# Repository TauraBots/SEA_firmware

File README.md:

# SEA_firmware
Firmware utilizado no atuador de serra elástica

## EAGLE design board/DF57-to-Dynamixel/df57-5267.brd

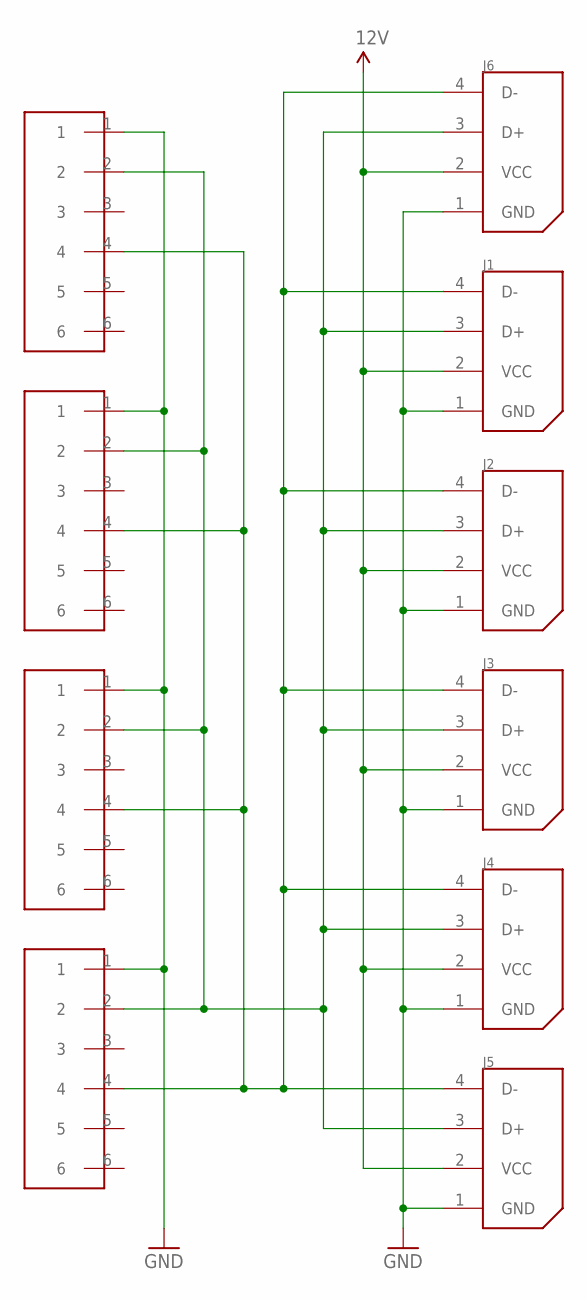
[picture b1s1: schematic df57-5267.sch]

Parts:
J1, J2, J3, J4, J5, J6: 22-03-5045; 5267-4
U$1, U$2, U$3, U$4: DF57-6P

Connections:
12V: J1.2 (VCC), J2.2 (VCC), J3.2 (VCC), J4.2 (VCC), J5.2 (VCC), J6.2 (VCC)
D+: J1.3 (D+), J2.3 (D+), J3.3 (D+), J4.3 (D+), J5.3 (D+), J6.3 (D+), U$1.2, U$2.2, U$3.2, U$4.2
D-: J1.4 (D-), J2.4 (D-), J3.4 (D-), J4.4 (D-), J5.4 (D-), J6.4 (D-), U$1.4, U$2.4, U$3.4, U$4.4
GND: J1.1 (GND), J2.1 (GND), J3.1 (GND), J4.1 (GND), J5.1 (GND), J6.1 (GND), U$1.1, U$2.1, U$3.1, U$4.1

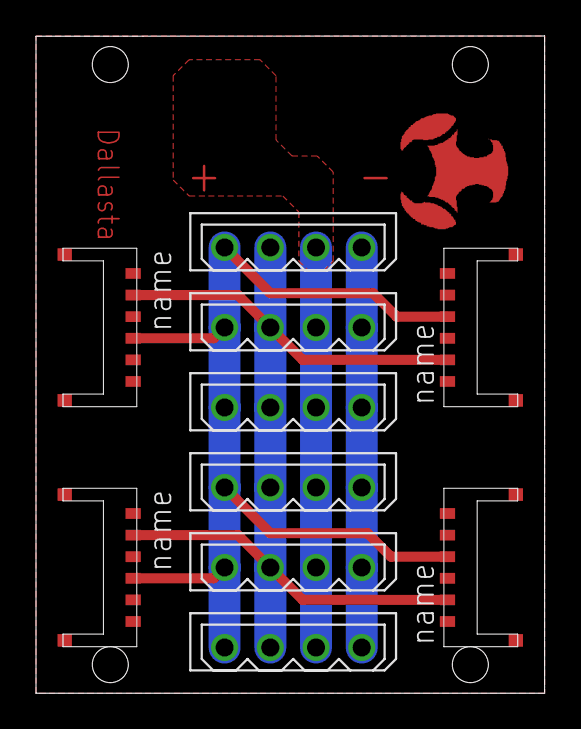
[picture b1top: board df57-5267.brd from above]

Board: 2 copper layers, 28.3 x 36.5 mm, 10 parts (0 on the bottom side), 4 nets.

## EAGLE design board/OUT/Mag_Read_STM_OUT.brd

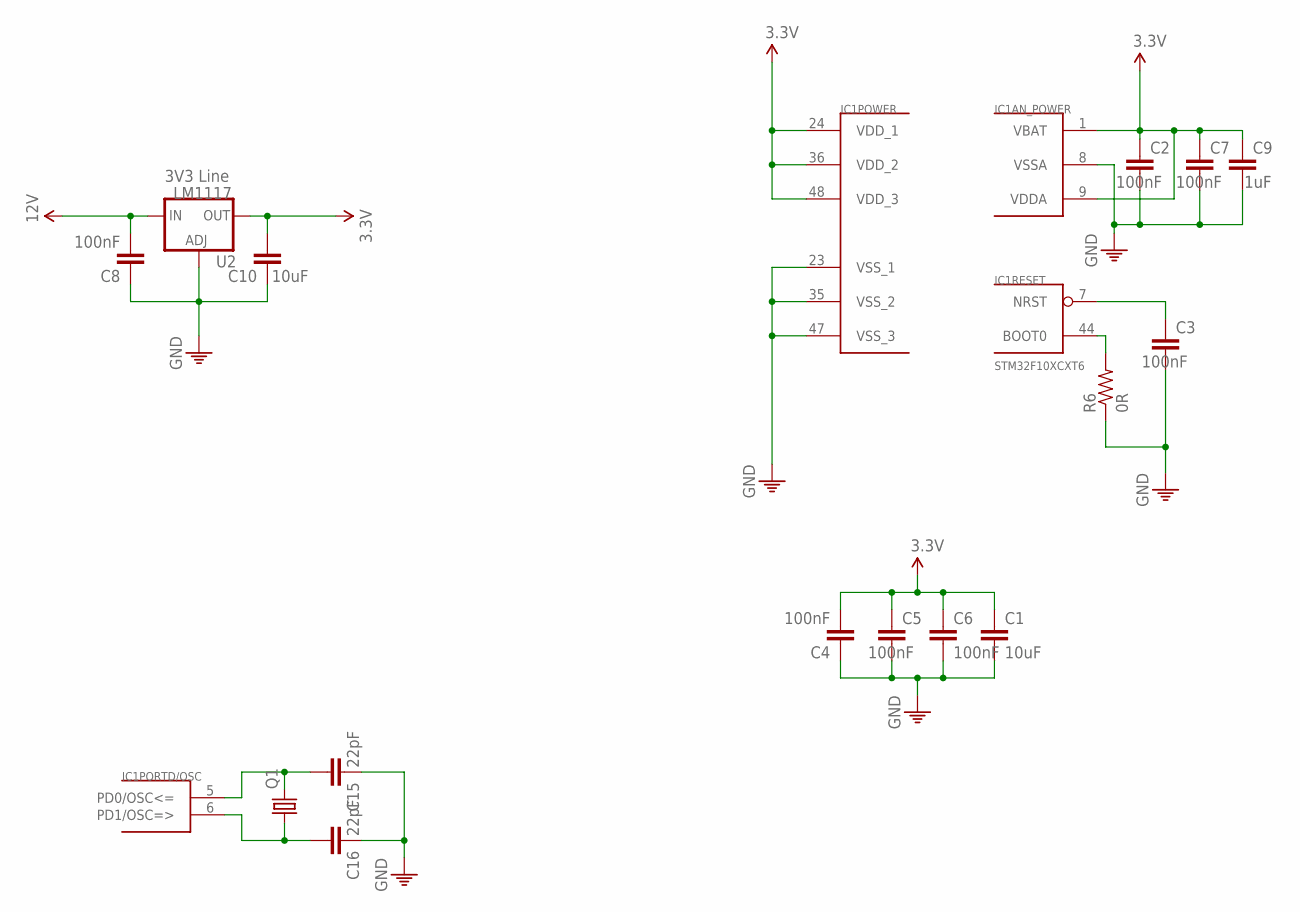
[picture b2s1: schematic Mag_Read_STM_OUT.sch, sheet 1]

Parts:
C1, C10: 10uF; C0603
C2, C3, C4, C5, C6, C7, C8: 100nF; C0603
C9: 1uF; C0603
C15, C16: 22pF; C0603
IC1: STM32F10XCXT6; TQFP48
Q1: CRYSTALCTS406; CTS406
R6: 0R; 0603-RES
U2: LM1117; SOT223

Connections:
3.3V: C1.1, C2.1, C4.2, C5.1, C6.1, C7.1, C9.1, C10.2, IC1.1 (VBAT), IC1.9 (VDDA), IC1.24 (VDD_1), IC1.36 (VDD_2), IC1.48 (VDD_3), U2.2 (OUT), U2.4 (OUT); also elsewhere on the board
12V: C8.2, U2.3 (IN); also elsewhere on the board
GND: C1.2, C2.2, C3.2, C4.1, C5.2, C6.2, C7.2, C8.1, C9.2, C10.1, C15.1, C16.1, IC1.8 (VSSA), IC1.23 (VSS_1), IC1.35 (VSS_2), IC1.47 (VSS_3), R6.1, U2.1 (ADJ); also elsewhere on the board
unnamed: C15.2, IC1.5 (PD0/OSC<=), Q1.3 (2)
unnamed: C16.2, IC1.6 (PD1/OSC=>), Q1.1
unnamed: IC1.44 (BOOT0), R6.2
NRST: C3.1, IC1.7 (NRST); also elsewhere on the board

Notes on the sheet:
3V3 Line

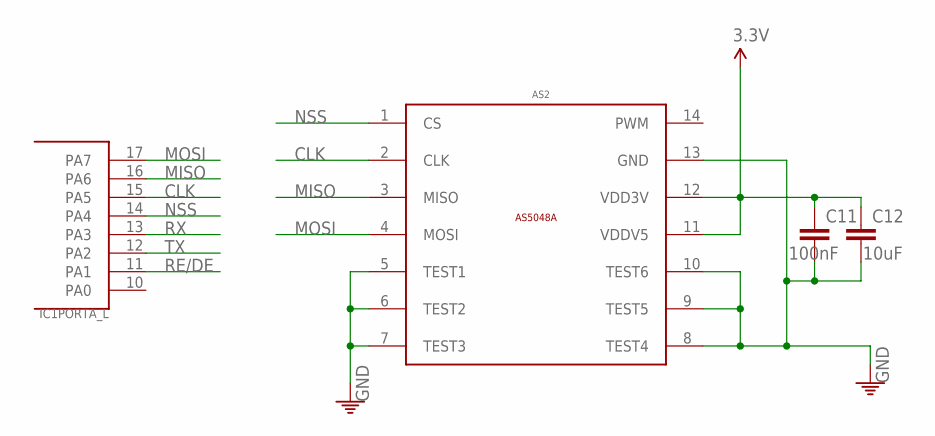
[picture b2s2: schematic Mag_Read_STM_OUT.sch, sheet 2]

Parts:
AS2: AS5048A_MAGNETIC_ROTARY_ENCODERTSSOP14; AS5048A_14-TSSOP
C11: 100nF; C0603
C12: 10uF; C0603
IC1: STM32F10XCXT6; TQFP48

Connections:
3.3V: AS2.11 (VDDV5), AS2.12 (VDD3V), C11.1, C12.1; also elsewhere on the board
CLK: AS2.2 (CLK), IC1.15 (PA5)
GND: AS2.5 (TEST1), AS2.6 (TEST2), AS2.7 (TEST3), AS2.8 (TEST4), AS2.9 (TEST5), AS2.10 (TEST6), AS2.13 (GND), C11.2, C12.2; also elsewhere on the board
MISO: AS2.3 (MISO), IC1.16 (PA6)
MOSI: AS2.4 (MOSI), IC1.17 (PA7)
NSS: AS2.1 (CS), IC1.14 (PA4)
RE/DE: IC1.11 (PA1); also elsewhere on the board
RX: IC1.13 (PA3); also elsewhere on the board
TX: IC1.12 (PA2); also elsewhere on the board

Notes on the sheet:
MISO
MOSI
NSS
CLK
RE/DE

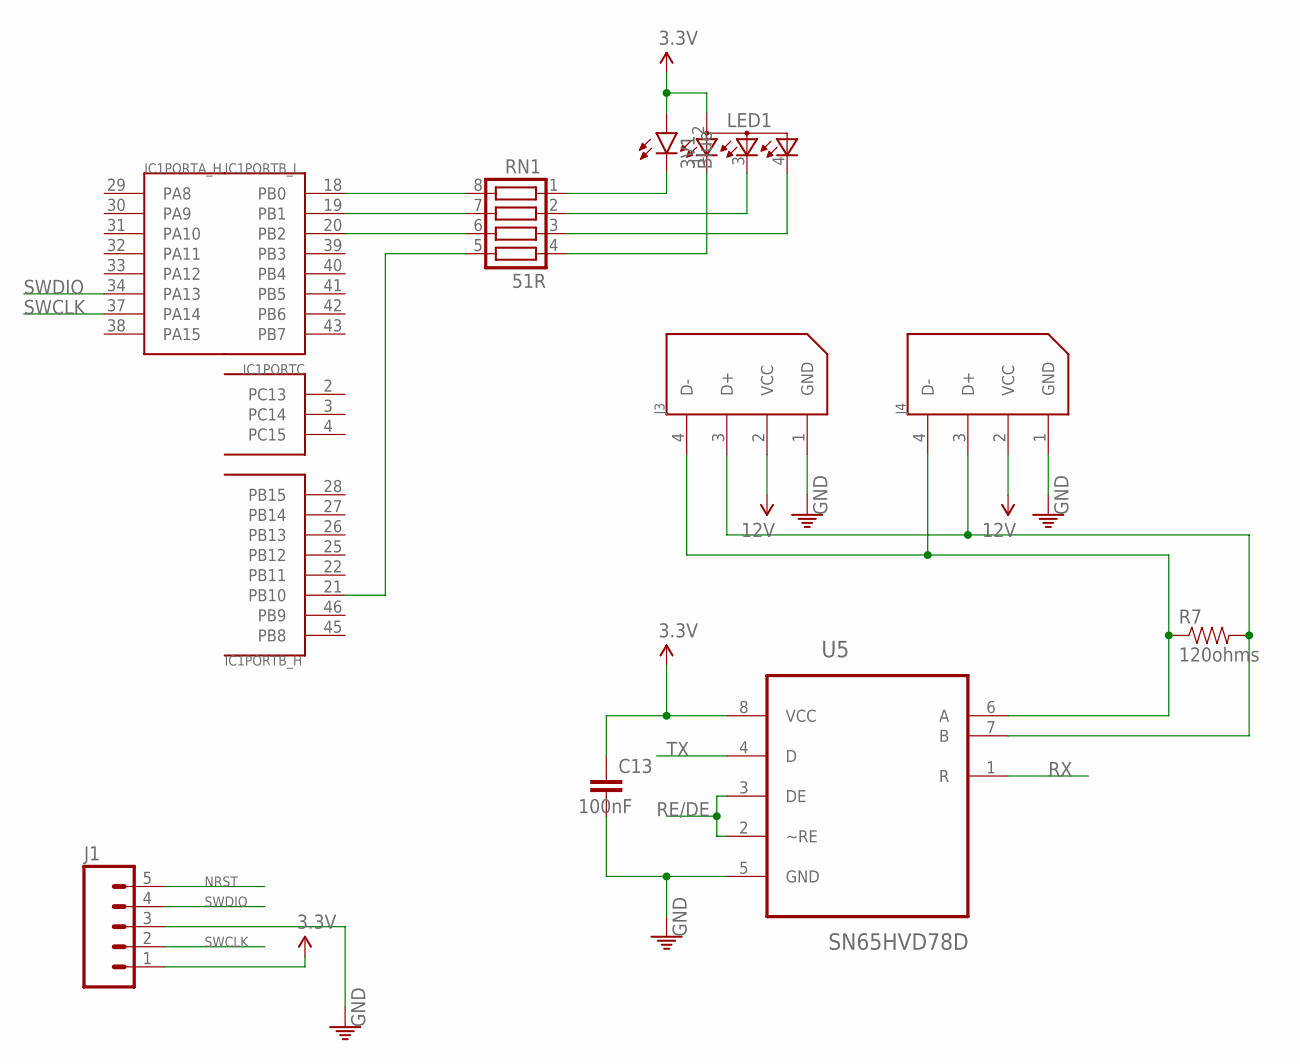
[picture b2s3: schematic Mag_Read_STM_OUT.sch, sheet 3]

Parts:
3V1: Blue; LED-0603
C13: 100nF; C0603
IC1: STM32F10XCXT6; TQFP48
J1: M05PTH; 1X05
J3, J4: 22-03-5045; 5267-4
LED1: TOPLED-3; P-LCC-4-3
R7: 120ohms; 0603-RES
RN1: 51R; CAY10-XXXJ4
U5: SN65HVD78D; SOIC127P600X175-8N

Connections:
3.3V: 3V1.A, C13.1, J1.1, LED1.2 (A2), U5.8 (VCC); also elsewhere on the board
12V: J3.2 (VCC), J4.2 (VCC); also elsewhere on the board
D_N: J3.4 (D-), J4.4 (D-), R7.1, U5.6 (A)
D_P: J3.3 (D+), J4.3 (D+), R7.2, U5.7 (B)
GND: C13.2, J1.3, J3.1 (GND), J4.1 (GND), U5.5 (GND); also elsewhere on the board
unnamed: LED1.1 (CRED), RN1.4
unnamed: LED1.4 (CGREEN), RN1.3
unnamed: LED1.3 (CBLUE), RN1.2
unnamed: 3V1.C, RN1.1
unnamed: IC1.21 (PB10), RN1.5
unnamed: IC1.20 (PB2), RN1.6
unnamed: IC1.19 (PB1), RN1.7
unnamed: IC1.18 (PB0), RN1.8
NRST: J1.5; also elsewhere on the board
RE/DE: U5.2 (~RE), U5.3 (DE); also elsewhere on the board
RX: U5.1 (R); also elsewhere on the board
SWCLK: IC1.37 (PA14), J1.2
SWDIO: IC1.34 (PA13), J1.4
TX: U5.4 (D); also elsewhere on the board

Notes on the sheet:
RE/DE
SWCLK
SWDIO
NRST

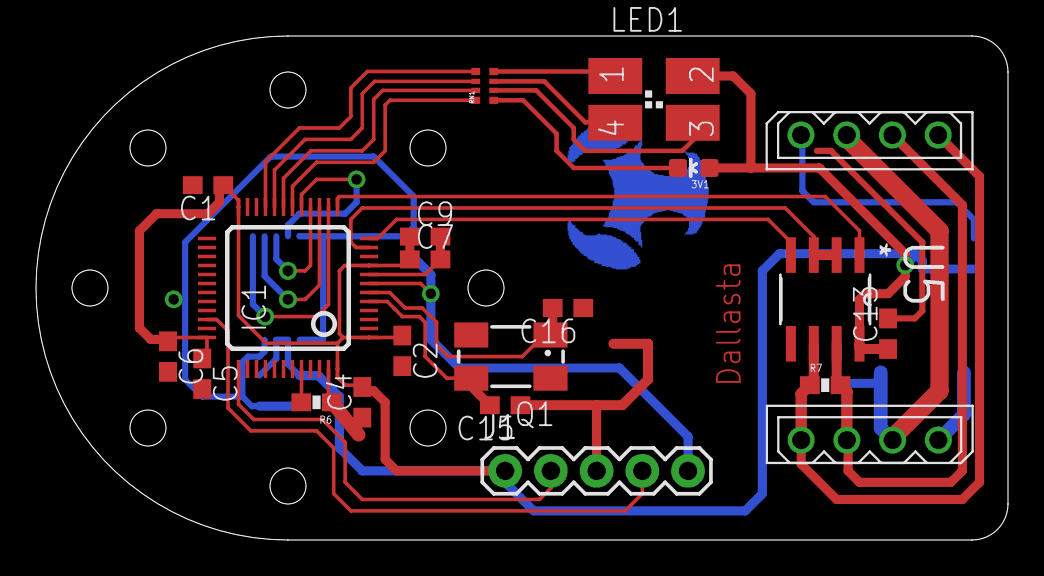
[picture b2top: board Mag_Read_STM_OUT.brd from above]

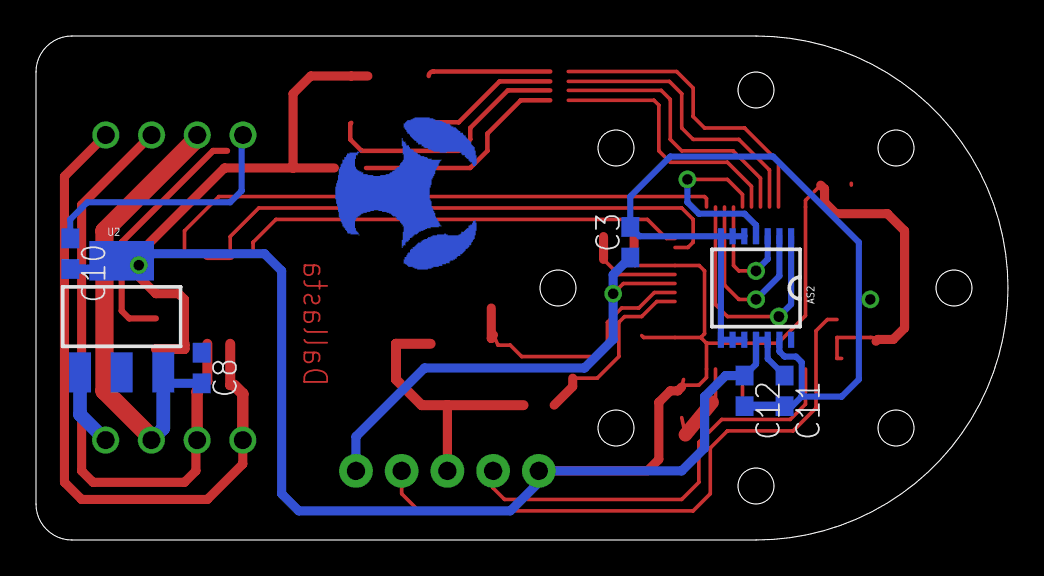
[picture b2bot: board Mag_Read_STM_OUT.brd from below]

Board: 2 copper layers, 54.0 x 28.0 mm, 28 parts (7 on the bottom side), 26 nets.

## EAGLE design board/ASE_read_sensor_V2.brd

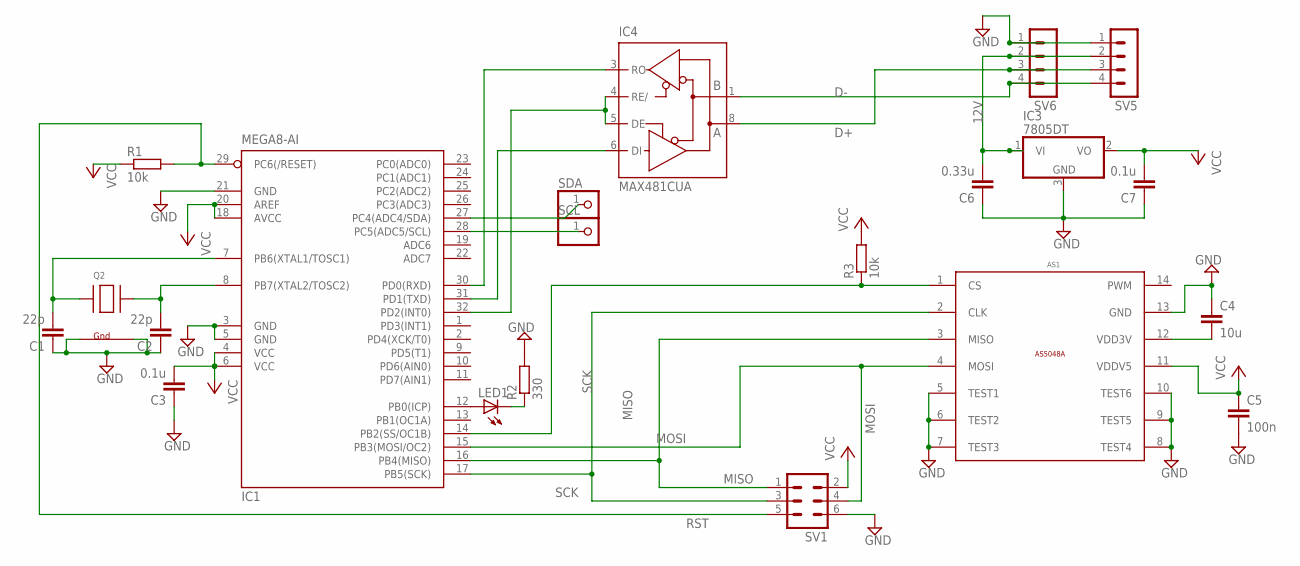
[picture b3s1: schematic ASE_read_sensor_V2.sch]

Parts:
AS1: AS5048A_MAGNETIC_ROTARY_ENCODERTSSOP14; AS5048A_14-TSSOP
C1, C2: 22p; C0603
C3, C7: 0.1u; C0603
C4: 10u; C0603
C5: 100n; C0603
C6: 0.33u; C0603
IC1: MEGA8-AI; TQFP32-08
IC3: 7805DT; TO252
IC4: MAX481CUA; UMAX8
LED1: LEDCHIPLED_0805; CHIPLED_0805
Q2: XTAL-4-3225; NX3225
R1, R3: 10k; R0603
R2: 330; R0603
SCL: PINHD-1X1CB; 1X01-CLEANBIG
SDA: PINHD-1X1CB; 1X01-CLEANBIG
SV1: MA03-2
SV5, SV6: MA04-1

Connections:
12V: C6.2, IC3.1 (VI), SV5.2, SV6.2
D+: IC4.8 (A), SV5.3, SV6.3
D-: IC4.1 (B), SV5.4, SV6.4
GND: AS1.5 (TEST1), AS1.6 (TEST2), AS1.7 (TEST3), AS1.8 (TEST4), AS1.9 (TEST5), AS1.10 (TEST6), AS1.13 (GND), C1.1, C2.1, C3.1, C4.1, C5.2, C6.1, C7.1, IC1.3 (GND), IC1.5 (GND), IC1.21 (GND), IC3.3 (GND), IC4.7 (GND), Q2.2 (G2), Q2.4 (G1), R2.2, SV1.6, SV5.1, SV6.1
MISO: AS1.3 (MISO), IC1.16 (PB4(MISO)), SV1.1
MOSI: AS1.4 (MOSI), IC1.15 (PB3(MOSI/OC2)), SV1.4
unnamed: C1.2, IC1.7 (PB6(XTAL1/TOSC1)), Q2.1 (X1)
unnamed: C2.2, IC1.8 (PB7(XTAL2/TOSC2)), Q2.3 (X2)
unnamed: IC1.12 (PB0(ICP)), LED1.A
unnamed: AS1.1 (CS), IC1.14 (PB2(SS/OC1B)), R3.1
unnamed: LED1.C, R2.1
unnamed: IC1.27 (PC4(ADC4/SDA)), SDA.1
unnamed: AS1.12 (VDD3V), C4.2
unnamed: IC1.28 (PC5(ADC5/SCL)), SCL.1
unnamed: IC1.30 (PD0(RXD)), IC4.3 (RO)
unnamed: IC1.31 (PD1(TXD)), IC4.6 (DI)
unnamed: IC1.32 (PD2(INT0)), IC4.4 (RE/), IC4.5 (DE)
RST: IC1.29 (PC6(/RESET)), R1.2, SV1.5
SCK: AS1.2 (CLK), IC1.17 (PB5(SCK)), SV1.3
VCC: AS1.11 (VDDV5), C3.2, C5.1, C7.2, IC1.4 (VCC), IC1.6 (VCC), IC1.18 (AVCC), IC1.20 (AREF), IC3.2 (VO), IC4.2 (VCC), R1.1, R3.2, SV1.2

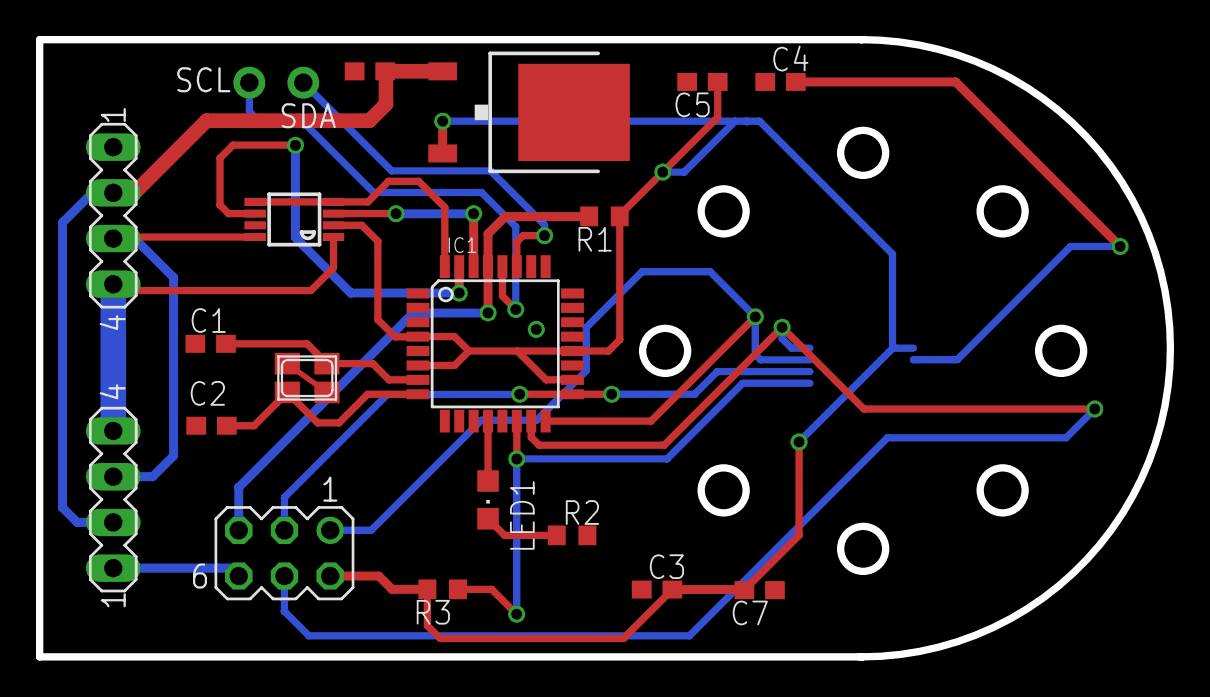
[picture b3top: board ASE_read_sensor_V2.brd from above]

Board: 2 copper layers, 62.8 x 34.3 mm, 21 parts (1 on the bottom side), 20 nets.

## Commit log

2016-05-19 Create fuses-atmeg168A

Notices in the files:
parts and their libraries:
SparkFun-Aesthetics: Licensing: Creative Commons ShareAlike 4.0 International - https://creativecommons.org/licenses/by-sa/4.0
